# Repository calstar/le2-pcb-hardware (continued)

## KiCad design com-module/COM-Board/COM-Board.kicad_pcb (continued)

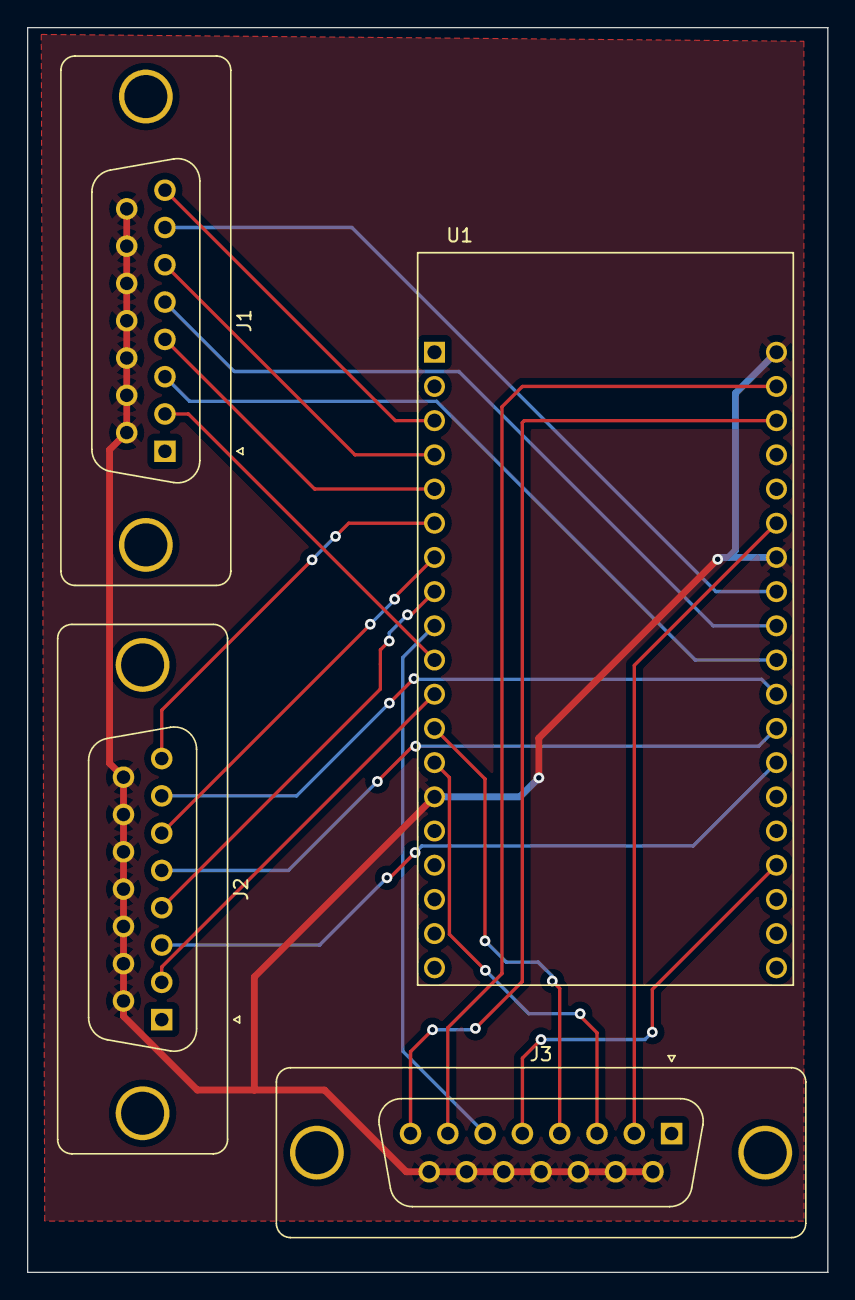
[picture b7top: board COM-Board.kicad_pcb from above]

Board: 2 copper layers, 59.4 x 92.5 mm, 4 parts (0 on the bottom side), 22 nets.

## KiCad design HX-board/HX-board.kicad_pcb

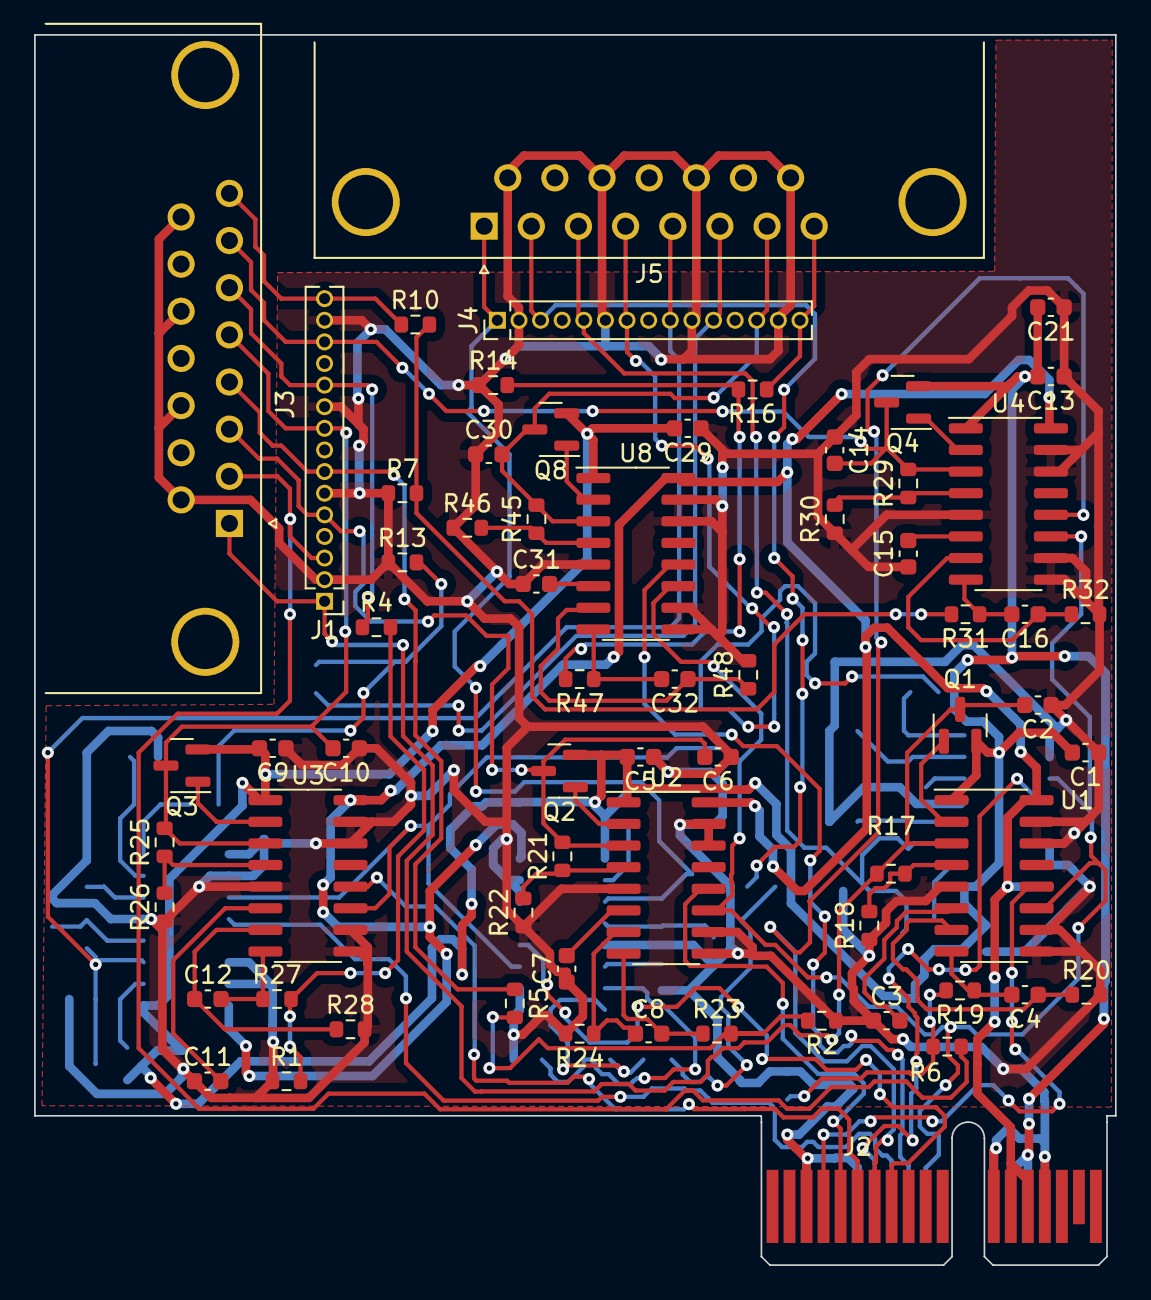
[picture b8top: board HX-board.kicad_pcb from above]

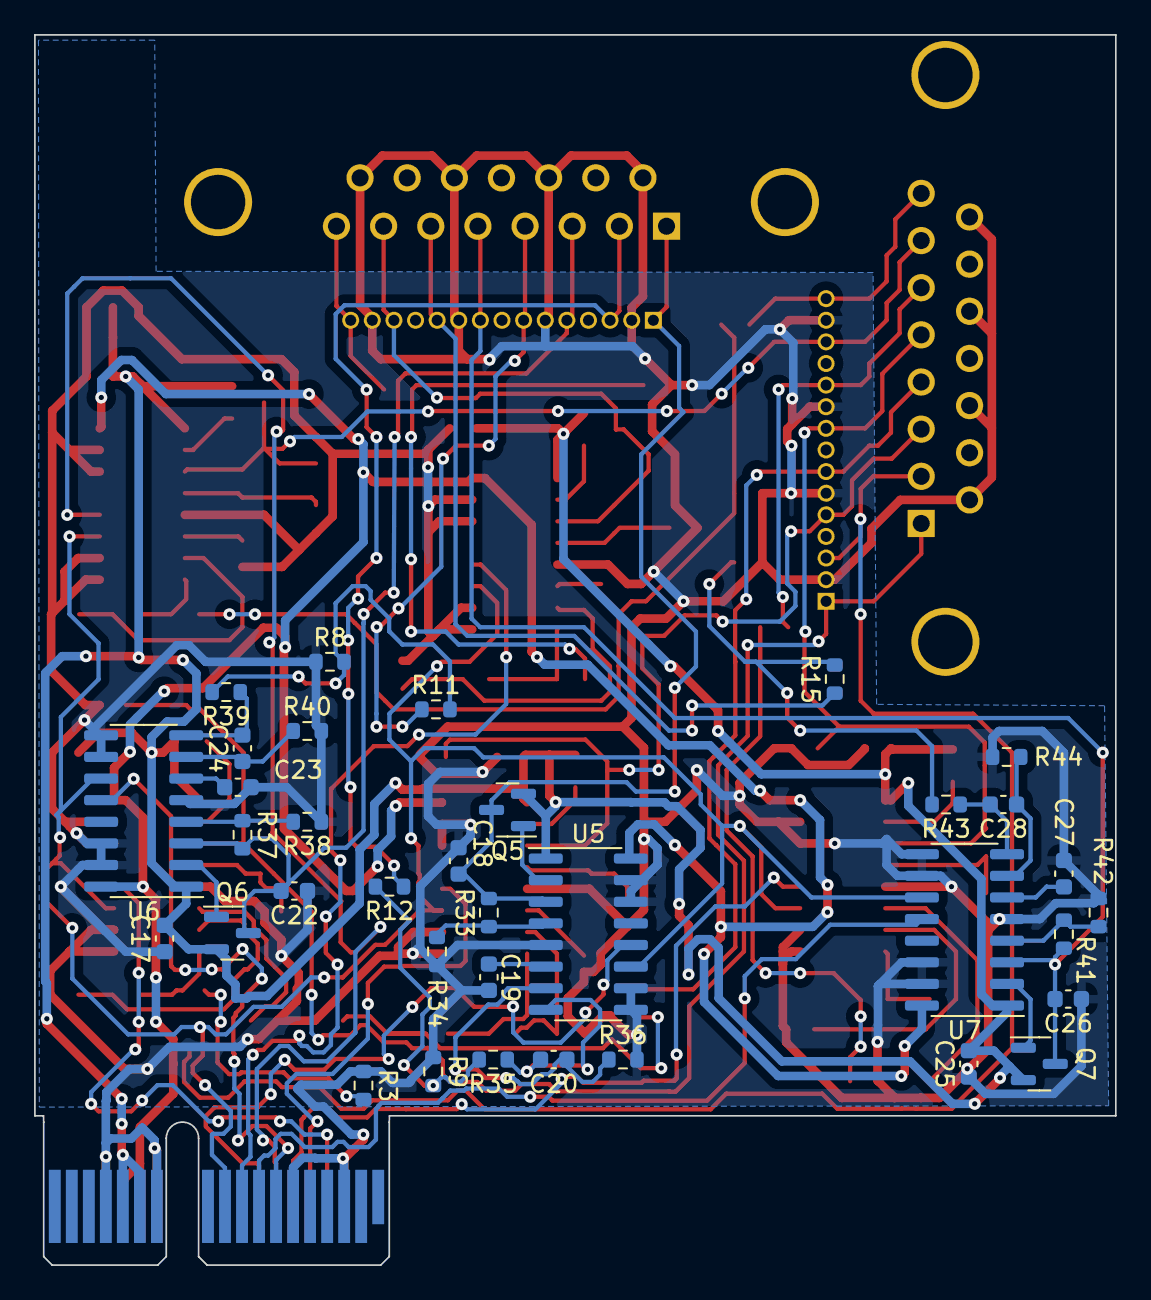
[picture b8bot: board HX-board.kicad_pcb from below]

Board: 2 copper layers, 63.5 x 72.3 mm, 101 parts (35 on the bottom side), 76 nets.

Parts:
C1, C2, C5, C6, C9, C10, C13, C14, C17, C18, C21, C22, C25, C26, C29, C30: 10uF; C_0603_1608Metric
C3, C4, C7, C8, C11, C12, C15, C16, C19, C20, C23, C24, C27, C28, C31, C32: 0.1uF; C_0603_1608Metric
J1, J4: Testpoints; PinHeader_1x15_P1.27mm_Vertical
J2: PCIE-LP-01-01-F-DV-A-TR; BUS_PCIexpress_x1
J3, J5: DB15_Female; DSUB_622-015-260-042
Q1, Q2, Q3, Q4, Q5, Q6, Q7, Q8: MMBT4403LT3G; SOT-23
R1, R2, R3, R7, R8, R9, R13, R14: 2kΩ; R_0603_1608Metric
R4, R5, R6, R10, R11, R12, R15, R16: 100kΩ; R_0603_1608Metric
R17, R21, R25, R29, R33, R37, R41, R45: 20kΩ; R_0603_1608Metric
R18, R22, R26, R30, R34, R38, R42, R46: 8.2kΩ; R_0603_1608Metric
R19, R20, R23, R24, R27, R28, R31, R32, R35, R36, R39, R40, R43, R44, R47, R48: 100Ω; R_0603_1608Metric
U1, U2, U3, U4, U5, U6, U7, U8: HX711; SOP-16_3.9x9.9mm_P1.27mm

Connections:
+3.3V: J2.B13, J2.B14, U1.16 (DVDD), U2.16 (DVDD), U3.16 (DVDD), U4.16 (DVDD), U5.16 (DVDD), U6.16 (DVDD), U7.16 (DVDD), U8.16 (DVDD)
+5V: C1.2, C5.2, C9.2, C13.2, C17.2, C21.2, C25.2, C29.2, J2.A13, J2.A14, Q1.2 (E), Q2.2 (E), Q3.2 (E), Q4.2 (E), Q5.2 (E), Q6.2 (E), Q7.2 (E), Q8.2 (E), U1.1 (VSUP), U2.1 (VSUP), U3.1 (VSUP), U4.1 (VSUP), U5.1 (VSUP), U6.1 (VSUP), U7.1 (VSUP), U8.1 (VSUP)
/HX1_A+: J1.3, J3.2, R6.1
/HX1_DT: J2.B4, U1.12 (DOUT)
/HX1_E+: C2.2, J1.1, J3.1, Q1.3 (C), R17.2, U1.3 (AVDD)
/HX2_A+: J1.7, J3.4, R5.1
/HX2_DT: J2.B5, U2.12 (DOUT)
/HX2_E+: C6.2, J1.5, J3.3, Q2.3 (C), R21.2, U2.3 (AVDD)
/HX3_A+: J1.11, J3.6, R4.1
/HX3_DT: J2.B6, U3.12 (DOUT)
/HX3_E+: C10.2, J1.9, J3.5, Q3.3 (C), R25.2, U3.3 (AVDD)
/HX4_A+: J1.15, J3.8, R10.1
/HX4_DT: J2.B7, U4.12 (DOUT)
/HX4_E+: C14.2, J1.13, J3.7, Q4.3 (C), R29.2, U4.3 (AVDD)
/HX5_A+: J4.3, J5.2, R12.1
/HX5_DT: J2.B8, U5.12 (DOUT)
/HX5_E+: C18.2, J4.1, J5.1, Q5.3 (C), R33.2, U5.3 (AVDD)
/HX6_A+: J4.7, J5.4, R11.1
/HX6_DT: J2.A7, U6.12 (DOUT)
/HX6_E+: C22.2, J4.5, J5.3, Q6.3 (C), R37.2, U6.3 (AVDD)
/HX7_A+: J4.11, J5.6, R15.1
/HX7_DT: J2.A8, U7.12 (DOUT)
/HX7_E+: C26.2, J4.9, J5.5, Q7.3 (C), R41.2, U7.3 (AVDD)
/HX8_A+: J4.15, J5.8, R16.1
/HX8_DT: J2.A9, U8.12 (DOUT)
/HX8_E+: C30.2, J4.13, J5.7, Q8.3 (C), R45.2, U8.3 (AVDD)
/HX711 1/A+: R3.2, R6.2, R19.2
/HX711 2/A+: R2.2, R5.2, R23.2
/HX711 3/A+: R1.2, R4.2, R27.2
/HX711 4/A+: R7.2, R10.2, R31.2
/HX711 5/A+: R9.2, R12.2, R35.2
/HX711 6/A+: R8.2, R11.2, R39.2
/HX711 7/A+: R13.2, R15.2, R43.2
/HX711 8/A+: R14.2, R16.2, R47.2
/HX_CLK: J2.A10, U1.11 (PD_SCK), U2.11 (PD_SCK), U3.11 (PD_SCK), U4.11 (PD_SCK), U5.11 (PD_SCK), U6.11 (PD_SCK), U7.11 (PD_SCK), U8.11 (PD_SCK)
GND: C1.1, C2.1, C3.1, C5.1, C6.1, C7.1, C9.1, C10.1, C11.1, C13.1, C14.1, C15.1, C17.1, C18.1, C19.1, C21.1, C22.1, C23.1, C25.1, C26.1, C27.1, C29.1, C30.1, C31.1, J1.2, J1.6, J1.10, J1.14, J2.A3, J2.A6, J2.A12, J2.A15, J2.B3, J2.B12, J2.B15, J3.9, J3.11 (P111), J3.13, J3.15, J4.2, J4.6, J4.10, J4.14, J5.9, J5.11 (P111), J5.13, J5.15, R1.1, R2.1, R3.1, R7.1, R8.1, R9.1, R13.1, R14.1, R18.1, R20.2, R22.1, R24.2, R26.1, R28.2, R30.1, R32.2, R34.1, R36.2, R38.1, R40.2, R42.1, R44.2, R46.1, R48.2, U1.5 (AGND), U1.9 (INB-), U1.10 (INB+), U1.14 (XI), U1.15 (RATE), U2.5 (AGND), U2.9 (INB-), U2.10 (INB+), U2.14 (XI), U2.15 (RATE), U3.5 (AGND), U3.9 (INB-), U3.10 (INB+), U3.14 (XI), U3.15 (RATE), U4.5 (AGND), U4.9 (INB-), U4.10 (INB+), U4.14 (XI), U4.15 (RATE), U5.5 (AGND), U5.9 (INB-), U5.10 (INB+), U5.14 (XI), U5.15 (RATE), U6.5 (AGND), U6.9 (INB-), U6.10 (INB+), U6.14 (XI), U6.15 (RATE), U7.5 (AGND), U7.9 (INB-), U7.10 (INB+), U7.14 (XI), U7.15 (RATE), U8.5 (AGND), U8.9 (INB-), U8.10 (INB+), U8.14 (XI), U8.15 (RATE)
unnamed: Q1.1 (B), U1.2 (BASE)
unnamed: R17.1, R18.2, U1.4 (VFB)
unnamed: C3.2, U1.6 (VBG)
unnamed: C4.1, R20.1, U1.7 (INA-)
unnamed: C4.2, R19.1, U1.8 (INA+)
unnamed: Q2.1 (B), U2.2 (BASE)
unnamed: R21.1, R22.2, U2.4 (VFB)
unnamed: C7.2, U2.6 (VBG)
unnamed: C8.1, R24.1, U2.7 (INA-)
unnamed: C8.2, R23.1, U2.8 (INA+)
unnamed: Q3.1 (B), U3.2 (BASE)
unnamed: R25.1, R26.2, U3.4 (VFB)
unnamed: C11.2, U3.6 (VBG)
unnamed: C12.1, R28.1, U3.7 (INA-)
unnamed: C12.2, R27.1, U3.8 (INA+)
unnamed: Q4.1 (B), U4.2 (BASE)
unnamed: R29.1, R30.2, U4.4 (VFB)
unnamed: C15.2, U4.6 (VBG)
unnamed: C16.1, R32.1, U4.7 (INA-)
unnamed: C16.2, R31.1, U4.8 (INA+)
unnamed: Q5.1 (B), U5.2 (BASE)
unnamed: R33.1, R34.2, U5.4 (VFB)
unnamed: C19.2, U5.6 (VBG)
unnamed: C20.1, R36.1, U5.7 (INA-)
unnamed: C20.2, R35.1, U5.8 (INA+)
unnamed: Q6.1 (B), U6.2 (BASE)
unnamed: R37.1, R38.2, U6.4 (VFB)
unnamed: C23.2, U6.6 (VBG)
unnamed: C24.1, R40.1, U6.7 (INA-)
unnamed: C24.2, R39.1, U6.8 (INA+)
unnamed: Q7.1 (B), U7.2 (BASE)
unnamed: R41.1, R42.2, U7.4 (VFB)
unnamed: C27.2, U7.6 (VBG)
unnamed: C28.1, R44.1, U7.7 (INA-)
unnamed: C28.2, R43.1, U7.8 (INA+)
unnamed: Q8.1 (B), U8.2 (BASE)
unnamed: R45.1, R46.2, U8.4 (VFB)
unnamed: C31.2, U8.6 (VBG)
unnamed: C32.1, R48.1, U8.7 (INA-)
unnamed: C32.2, R47.1, U8.8 (INA+)

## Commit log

2023-08-22 power board schematic
2023-08-23 Current progress for HX and TC board.
2023-08-24 mosfet board
2023-08-28 Updated HX, TC boards.
2023-08-29 hardware-sch-blocks added
2023-08-29 core board
2023-08-29 core board schematic
2023-08-30 board updates
2023-08-30 more smol updates
2023-08-30 Updated schematics of TC,PT
2023-09-01 Updated mosfet schematics
2023-09-03 Replaced mosfet board with Conor's design using BTS3080EJXUMA1. Modified max31855 symbol to have A (separate assembly) reference designator.
2023-09-05 Updated HX, TC, and MOSFET board.
2023-09-05 core board pinouts
2023-09-06 Updated pcie and fixed HX, MOSFET, TC board. Also added hierarchical sheet.
2023-09-08 Basic routing for MOSFET board. Need silkscreen update.
2023-09-09 updates for layout MOSFET/HX
2023-09-10 Finished mosfet layout
2023-09-11 Finished Updating the HX Board
2023-09-11 TC Board (mostly done) and HX Board Done (Mostly)
2023-09-11 Fixed TC
2023-09-11 Revert "HX and TC Board mostly finished"
2023-09-11 Revert "Revert "HX and TC Board mostly finished""
    This reverts commit 2ae13608b6027366e1c59111a8dca91d16e06deb.
2023-09-12 TC Board Done
2023-09-12 HX and TC Done
2023-09-12 HX Board
    Forgot to put GND screen on back
2023-09-12 Finalize core board schematics.
2023-09-12 wired pcie together in core board.
2023-09-13 Finish tracing core board. Need to do cleanup and silkscreen.
2023-09-13 Finished core board.
2023-09-14 Fixed labels for TC Board
2023-09-14 final vers
2023-09-15 Generated PCB Manufactures
2023-09-15 Organized files for Gerber
2023-09-28 Updated TC gerber
2023-09-28 tc drill files
2023-10-22 MOSFET Board Updated
    MOSFET Board changes, new PCB Design and updated schematic.
2023-10-22 MOSFET Board Updated (Part II)
    Added double header GPIO and should be fine now :P
2023-10-22 Updated MOSFET (part III)
    Made sure there were 0 errors.
2023-10-23 MOSFET Board Updated (Part IV? I lost count)
    Has a specified op amp, fixed measurements, should be a double header GPIO, I believe that everything is connected. The only warnings are either silk screen or non labeled items, which should be fine.
2023-10-23 Gerber files + Drill Files
    I think that's all?
2023-10-23 Extra Files for MOSFET order
    I think these are right?
2024-01-03 Progress on revising ground boards.
2024-01-04 Further revision. Two batteries system.
2024-01-04 Added level shifter for gpio expander.
2024-01-04 Added an spi expander to core board.
2024-01-07 Revising PCIe.
2024-01-08 Ironing out small details, changed pcf8575 to IC instead of breakout.
2024-01-27 Separated into ground/flight/com system
2024-01-27 removed old files
2024-01-27 COM Board
    hi.
2024-01-30 Skeleton for flight module.
2024-01-30 Added a gpio expander to power board.
2024-01-31 skeleton for connector board
2024-02-09 power board updated
2024-02-09 worked on core-board schematic. Not done.
2024-02-11 updated power board.
2024-02-11 Updated core-board
2024-02-13 update on flight pcbs
2024-02-13 added diodes to 'OR' REDS-vent with on-board mosfets.
2024-02-13 mux update
2024-02-13 mux changes
2024-02-13 fixed mux capacitor
2024-02-14 Updated power mux circuit.
2024-02-18 16X symbol setup and mosfet schematic
2024-02-18 mosfet routing
2024-02-18 custom locking pcie footprint added TT
2024-02-18 changed to one battery
2024-02-18 mosfet board updates. GND tracing removals and aux scl/sda
2024-02-18 replaced IC
2024-02-19 finished power board?
2024-02-19 power board done
2024-02-19 Commit changes to the Connector
2024-02-19 update to sch
2024-02-19 updated symbol
2024-02-19 PCIe symbol update
2024-02-19 Updates to traces in TC board and updates PCIe connector
2024-02-19 core, mosfet
2024-02-19 fixed drc errors
2024-02-19 gerbers added
2024-02-20 added gnd to new ic on power board
2024-02-21 fixed a few erc errors on power board
2024-02-21 Progress on core board.
2024-02-21 board comments
2024-02-21 power board
2024-02-22 Edited the connector board to make sense
2024-02-22 changed the flags, checked for ERC <3
2024-02-22 did some power board layout
2024-02-22 commit edits to the schematic to reflect new pinouts
2024-02-23 some changes
2024-02-23 Finished flight-core.
2024-02-23 routing not done
2024-02-24 completed routing
2024-02-24 ignore this commit
2024-02-25 Commit - corrections from Dulanya
2024-02-25 Updated core board.
2024-02-25 hardware-sch-blocks/
2024-02-25 power board done?
2024-02-25 Commit edits part 2
2024-02-25 adding schottky for power
2024-02-25 Merged power board
2024-02-25 added star logo onto power board
2024-02-25 Removed artifacts from base directory.
2024-02-25 commit - pretty much final unless any major concerns are discovered.
2024-02-25 fixed some power board issues
2024-02-25 removed 3.3v planes
2024-02-26 final boards orderedd
2024-03-22 power v2
2024-03-23 Minor changes to footprint library
2024-03-24 leds + redundancy, still getting footprint errors
2024-03-24 fixed footprint courtyard errors
2024-03-24 actual footprint courtyard updates
2024-03-24 fixed all errors
2024-03-25 not done just commiting just in case
2024-03-25 more updates to flight power
2024-03-25 change the USB layout
2024-03-26 finished the connector board
2024-03-26 board review updates done
2024-03-26 connector fix - change to SMD
2024-03-26 added silkscreen cover
2024-03-26 power manufacturing
2024-03-26 connector board updates for manufacturing
2024-03-26 connector gerbs
2024-03-26 in the middle of updating micro usb
2024-03-26 still updating micro usb
2024-03-26 ON GOD ITS DONE
2024-03-26 manufacturing files or core
2024-03-29 components list
2024-03-29 parts list
2024-04-20 gitignore hwsch
2024-05-01 zipping files no changes lol
2024-05-01 more zipping
2024-05-02 core board sd card and HX2 HX6 changes
2024-05-08 quick updates to manufacturing
2024-05-10 core usb
